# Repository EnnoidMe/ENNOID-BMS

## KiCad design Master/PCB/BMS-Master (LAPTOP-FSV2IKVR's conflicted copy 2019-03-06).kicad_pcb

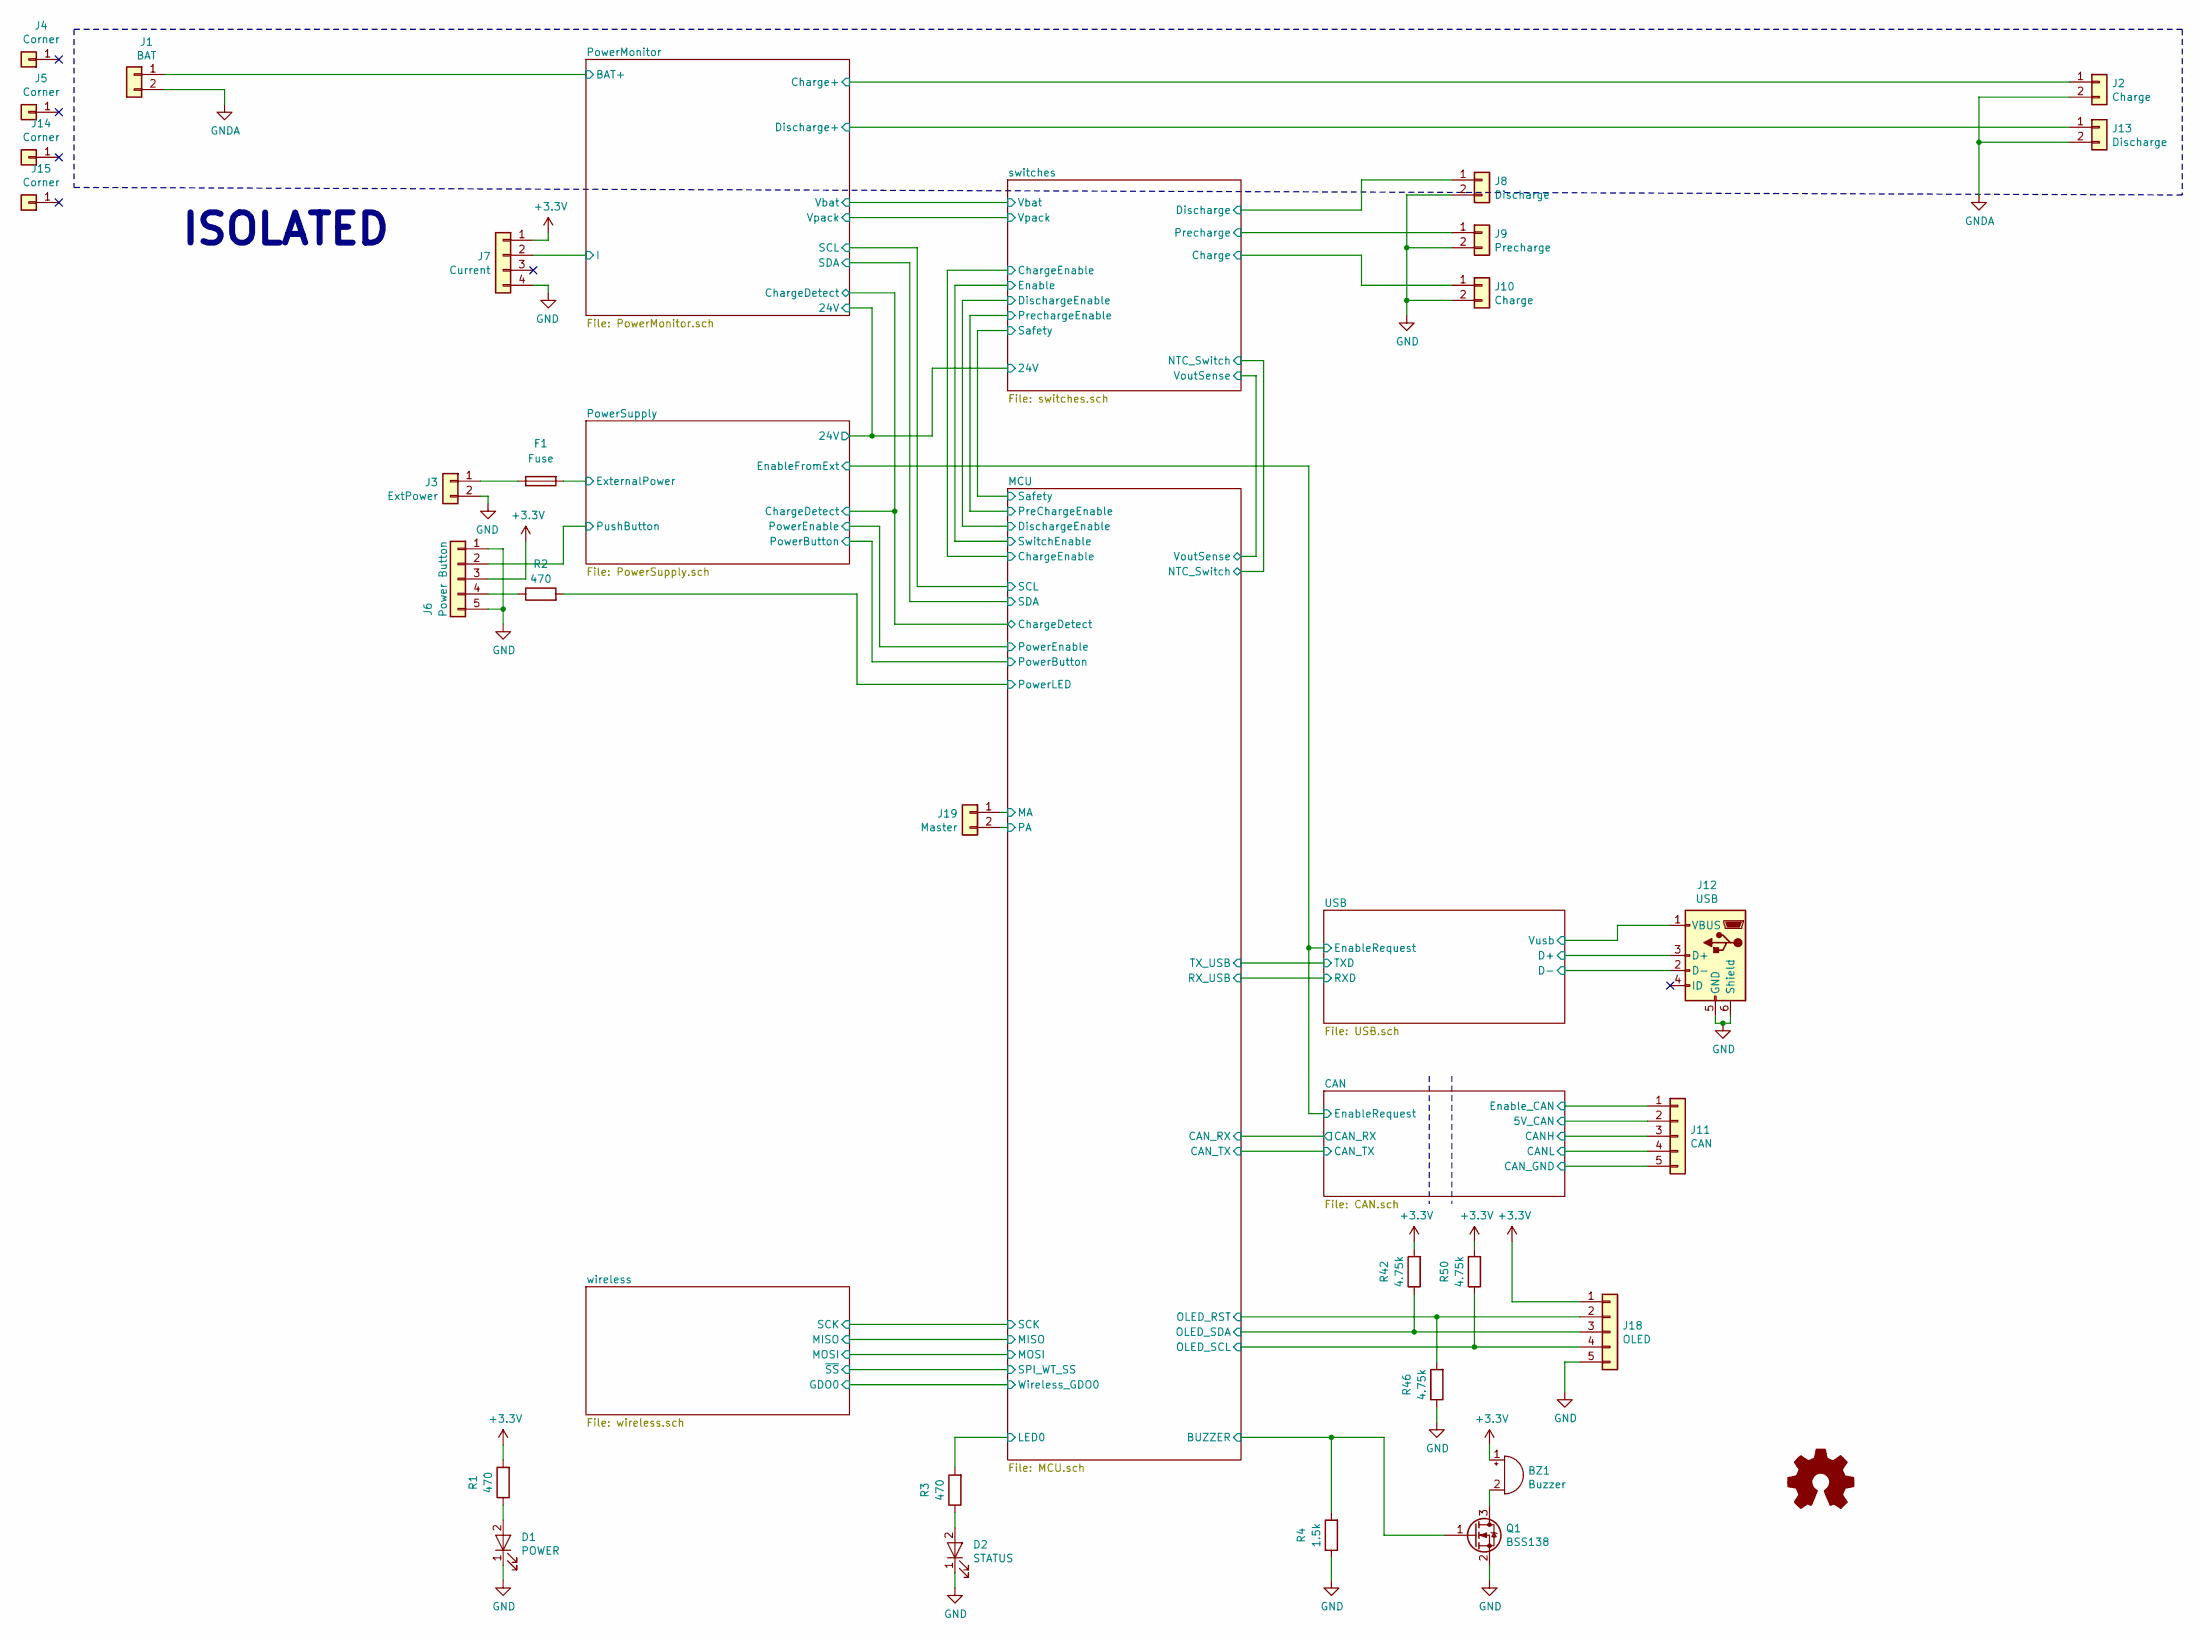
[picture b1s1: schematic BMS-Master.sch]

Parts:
BZ1: Buzzer; PUIAudio_SMT_0825_S_4_R
D1: POWER; LED_0603_HandSoldering
D2: STATUS; LED_0603_HandSoldering
F1: Fuse; Fuse_SMD1206_HandSoldering
J1: BAT; TerminalBlock_RND_205-00001_Pitch5.00mm
J2: Charge; TerminalBlock_RND_205-00001_Pitch5.00mm
J3: ExtPower; Molex_KK-6410-02_02x2.54mm_Straight
J4, J5, J14, J15: Corner; MountingHole_2.7mm_M2.5_Pad_Via
J6: Power Button; Molex_PicoBlade_53398-0571_05x1.25mm_Straight
J7: Current; Molex_KK-6410-04_04x2.54mm_Straight
J8: Discharge; Molex_KK-6410-02_02x2.54mm_Straight
J9: Precharge; Molex_KK-6410-02_02x2.54mm_Straight
J10: Charge; Molex_KK-6410-02_02x2.54mm_Straight
J11: CAN; Molex_PicoBlade_53261-0571_05x1.25mm_Angled
J12: USB; USB_Micro-B_Molex_47346-0001
J13: Discharge; TerminalBlock_RND_205-00001_Pitch5.00mm
J18: OLED; Molex_PicoBlade_53398-0571_05x1.25mm_Straight
J19: Master; Molex_KK-6410-02_02x2.54mm_Straight
LOGO1: Logo_Open_Hardware_Small; ENNOID-LOGO
Q1: BSS138; SOT-23
R1, R2, R3: 470; R_0603_HandSoldering
R4: 1.5k; R_0603_HandSoldering
R42, R46, R50: 4.75k; R_0603_HandSoldering

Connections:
/CAN/5V_CAN: J11.2; also elsewhere on the board
/CAN/CANH: J11.3; also elsewhere on the board
/CAN/CANL: J11.4; also elsewhere on the board
/CAN/CAN_GND: J11.5; also elsewhere on the board
/CAN/Enable_CAN: J11.1; also elsewhere on the board
/MCU/BUZZER: Q1.1 (G), R4.2; also elsewhere on the board
/MCU/LED0: R3.2; also elsewhere on the board
/MCU/MA: J19.1; also elsewhere on the board
/MCU/OLED_RST: J18.2, R46.2; also elsewhere on the board
/MCU/OLED_SCL: J18.4, R50.1; also elsewhere on the board
/MCU/OLED_SDA: J18.3, R42.1; also elsewhere on the board
/MCU/PA: J19.2; also elsewhere on the board
/MCU/PowerLED: R2.2; also elsewhere on the board
/PowerMonitor/24V: F1.2; also elsewhere on the board
/PowerMonitor/BAT+: J1.1; also elsewhere on the board
/PowerMonitor/Charge+: J2.1; also elsewhere on the board
/PowerMonitor/Discharge+: J13.1; also elsewhere on the board
/PowerMonitor/I: J7.2; also elsewhere on the board
/PowerSupply/PushButton: J6.2; also elsewhere on the board
/USB/D+: J12.3 (D+); also elsewhere on the board
/USB/D-: J12.2 (D-); also elsewhere on the board
/switches/Charge: J10.1; also elsewhere on the board
/switches/Discharge: J8.1; also elsewhere on the board
/switches/Precharge: J9.1; also elsewhere on the board
GND: D1.1 (K), D2.1 (K), J3.2, J6.1, J6.5, J7.4, J8.2, J9.2, J10.2, J12.5 (GND), J12.6 (Shield), J18.5, Q1.2 (S), R4.1, R46.1; also elsewhere on the board
GNDA: J1.2, J2.2, J13.2; also elsewhere on the board
unnamed: BZ1.2 (+), Q1.3 (D)
unnamed: D1.2 (A), R1.1
unnamed: D2.2 (A), R3.1
unnamed: F1.1, J3.1
unnamed: J6.4, R2.1
VDD: J12.1 (VBUS); also elsewhere on the board

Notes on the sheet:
ISOLATED

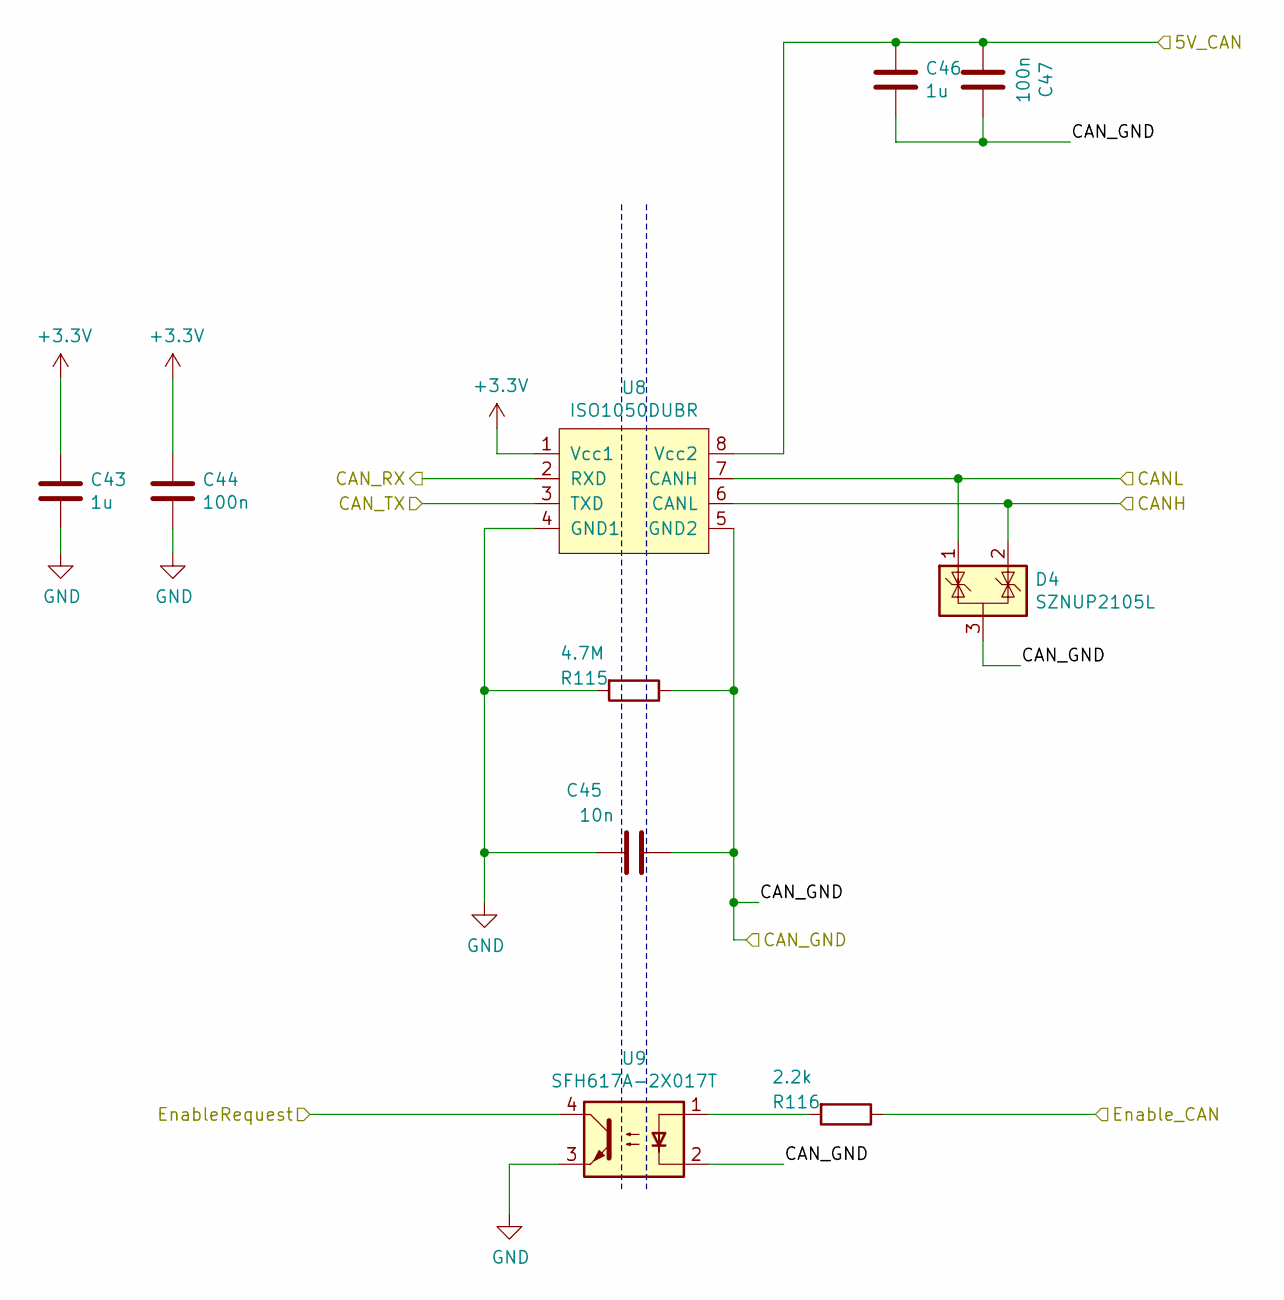
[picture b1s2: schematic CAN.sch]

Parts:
C43, C46: 1u; C_0805_HandSoldering
C44, C47: 100n; C_0603_HandSoldering
C45: 10n; C_0805_HandSoldering; Voltage 100V
D4: SZNUP2105L; SOT-23
R115: 4.7M; C_0805_HandSoldering; Voltage 100V
R116: 2.2k; C_0603_HandSoldering; Voltage 100V
U8: ISO1050DUBR; ISO1050
U9: SFH617A-2X017T; SMDIP-4_W9.53mm_Clearance8mm

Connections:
/CAN/5V_CAN: C46.1, C47.2, U8.8 (Vcc2); also elsewhere on the board
/CAN/CANH: D4.2 (K), U8.6 (CANL); also elsewhere on the board
/CAN/CANL: D4.1 (K), U8.7 (CANH); also elsewhere on the board
/CAN/CAN_GND: C45.1, C46.2, C47.1, D4.3 (A), R115.1, U8.5 (GND2), U9.2; also elsewhere on the board
/CAN/CAN_RX: U8.2 (RXD); also elsewhere on the board
/CAN/CAN_TX: U8.3 (TXD); also elsewhere on the board
/CAN/Enable_CAN: R116.1; also elsewhere on the board
/PowerSupply/EnableFromExt: U9.4; also elsewhere on the board
GND: C43.2, C44.2, C45.2, R115.2, U8.4 (GND1), U9.3; also elsewhere on the board
unnamed: R116.2, U9.1

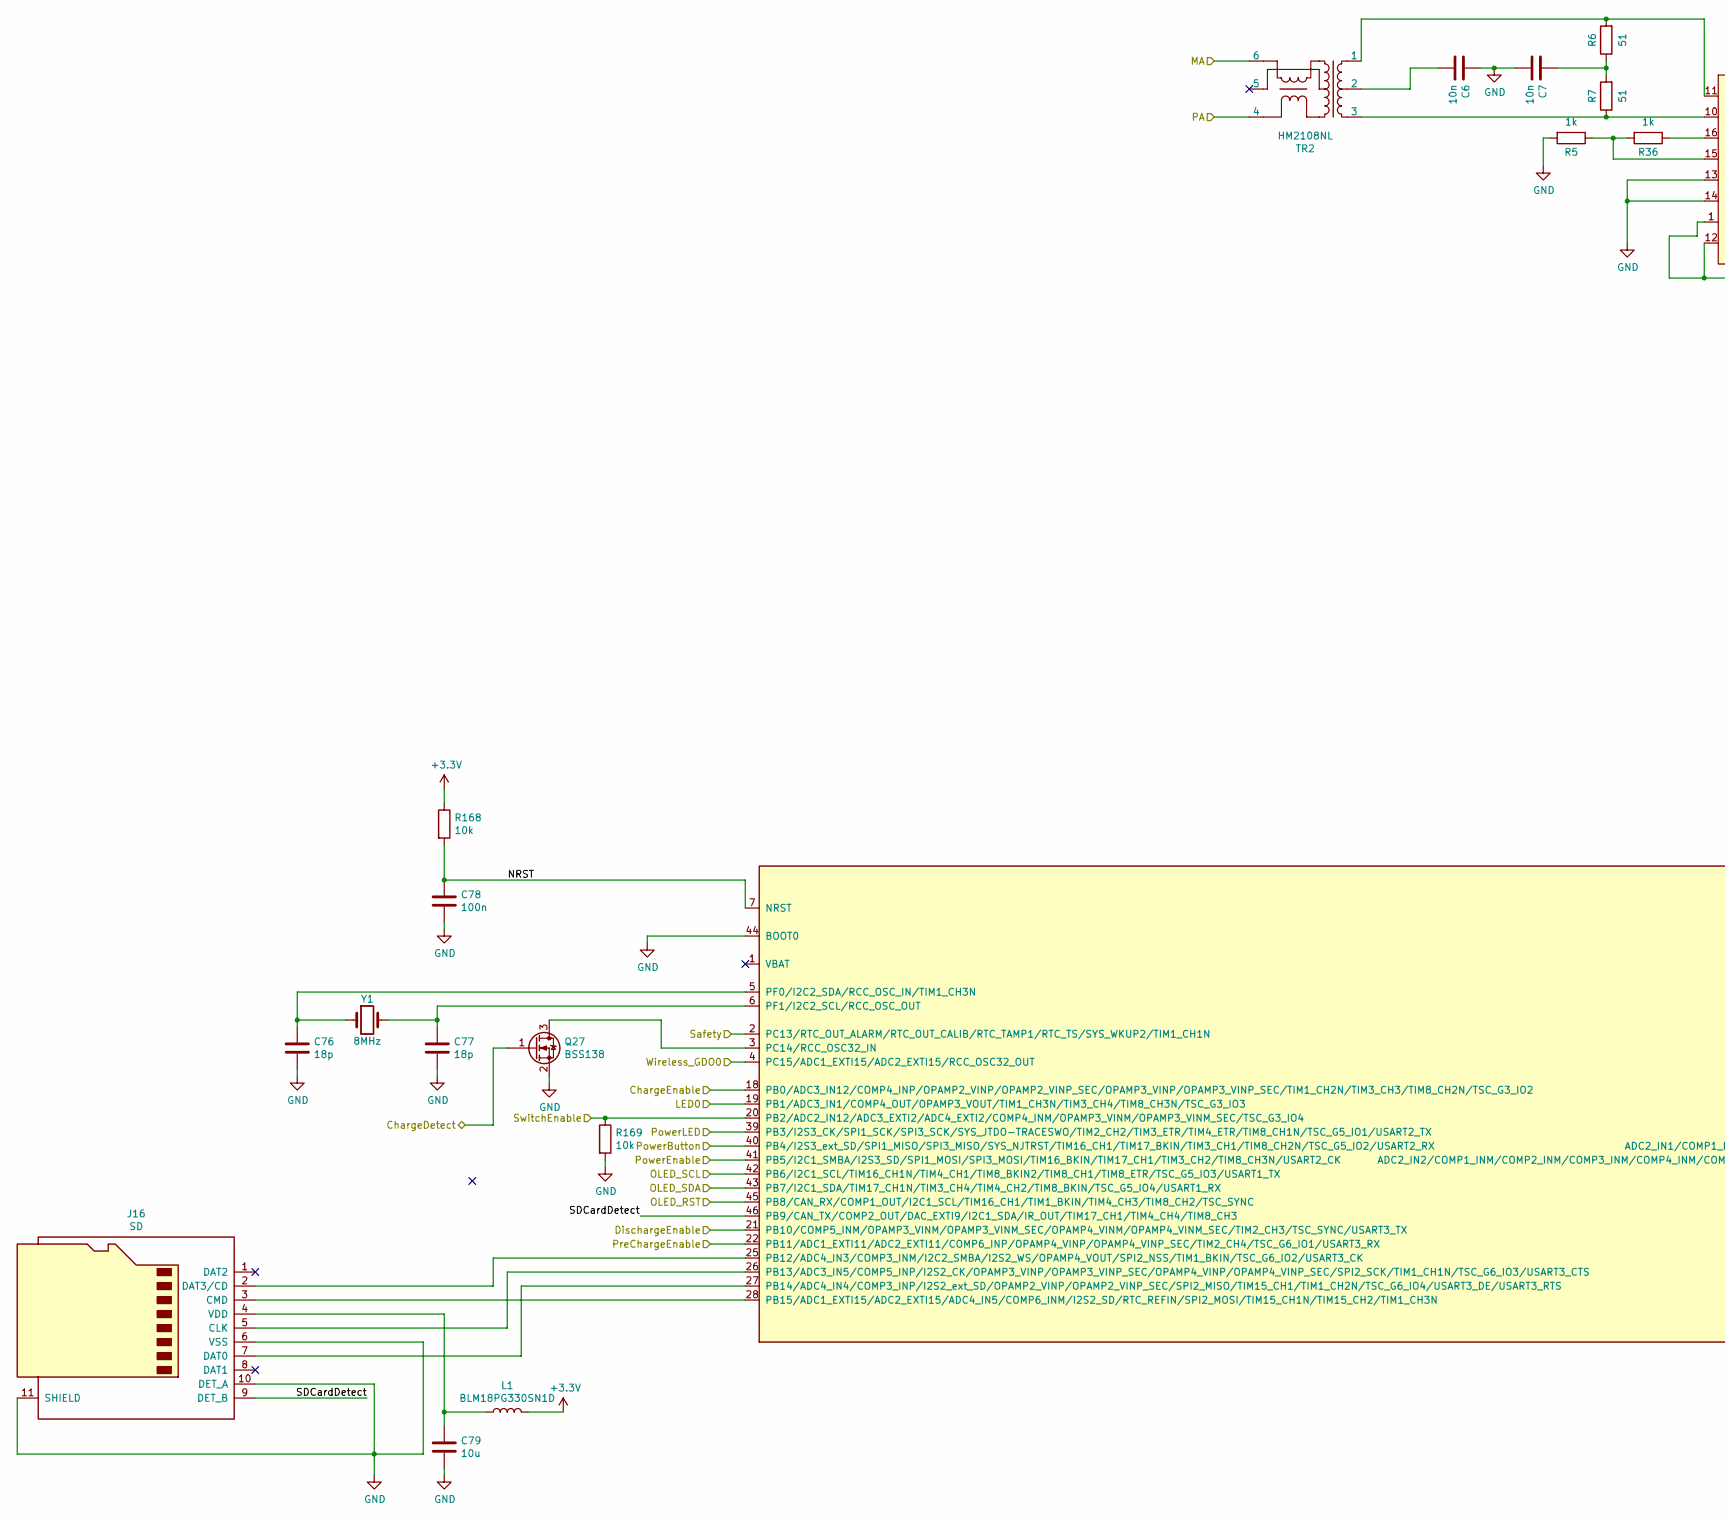
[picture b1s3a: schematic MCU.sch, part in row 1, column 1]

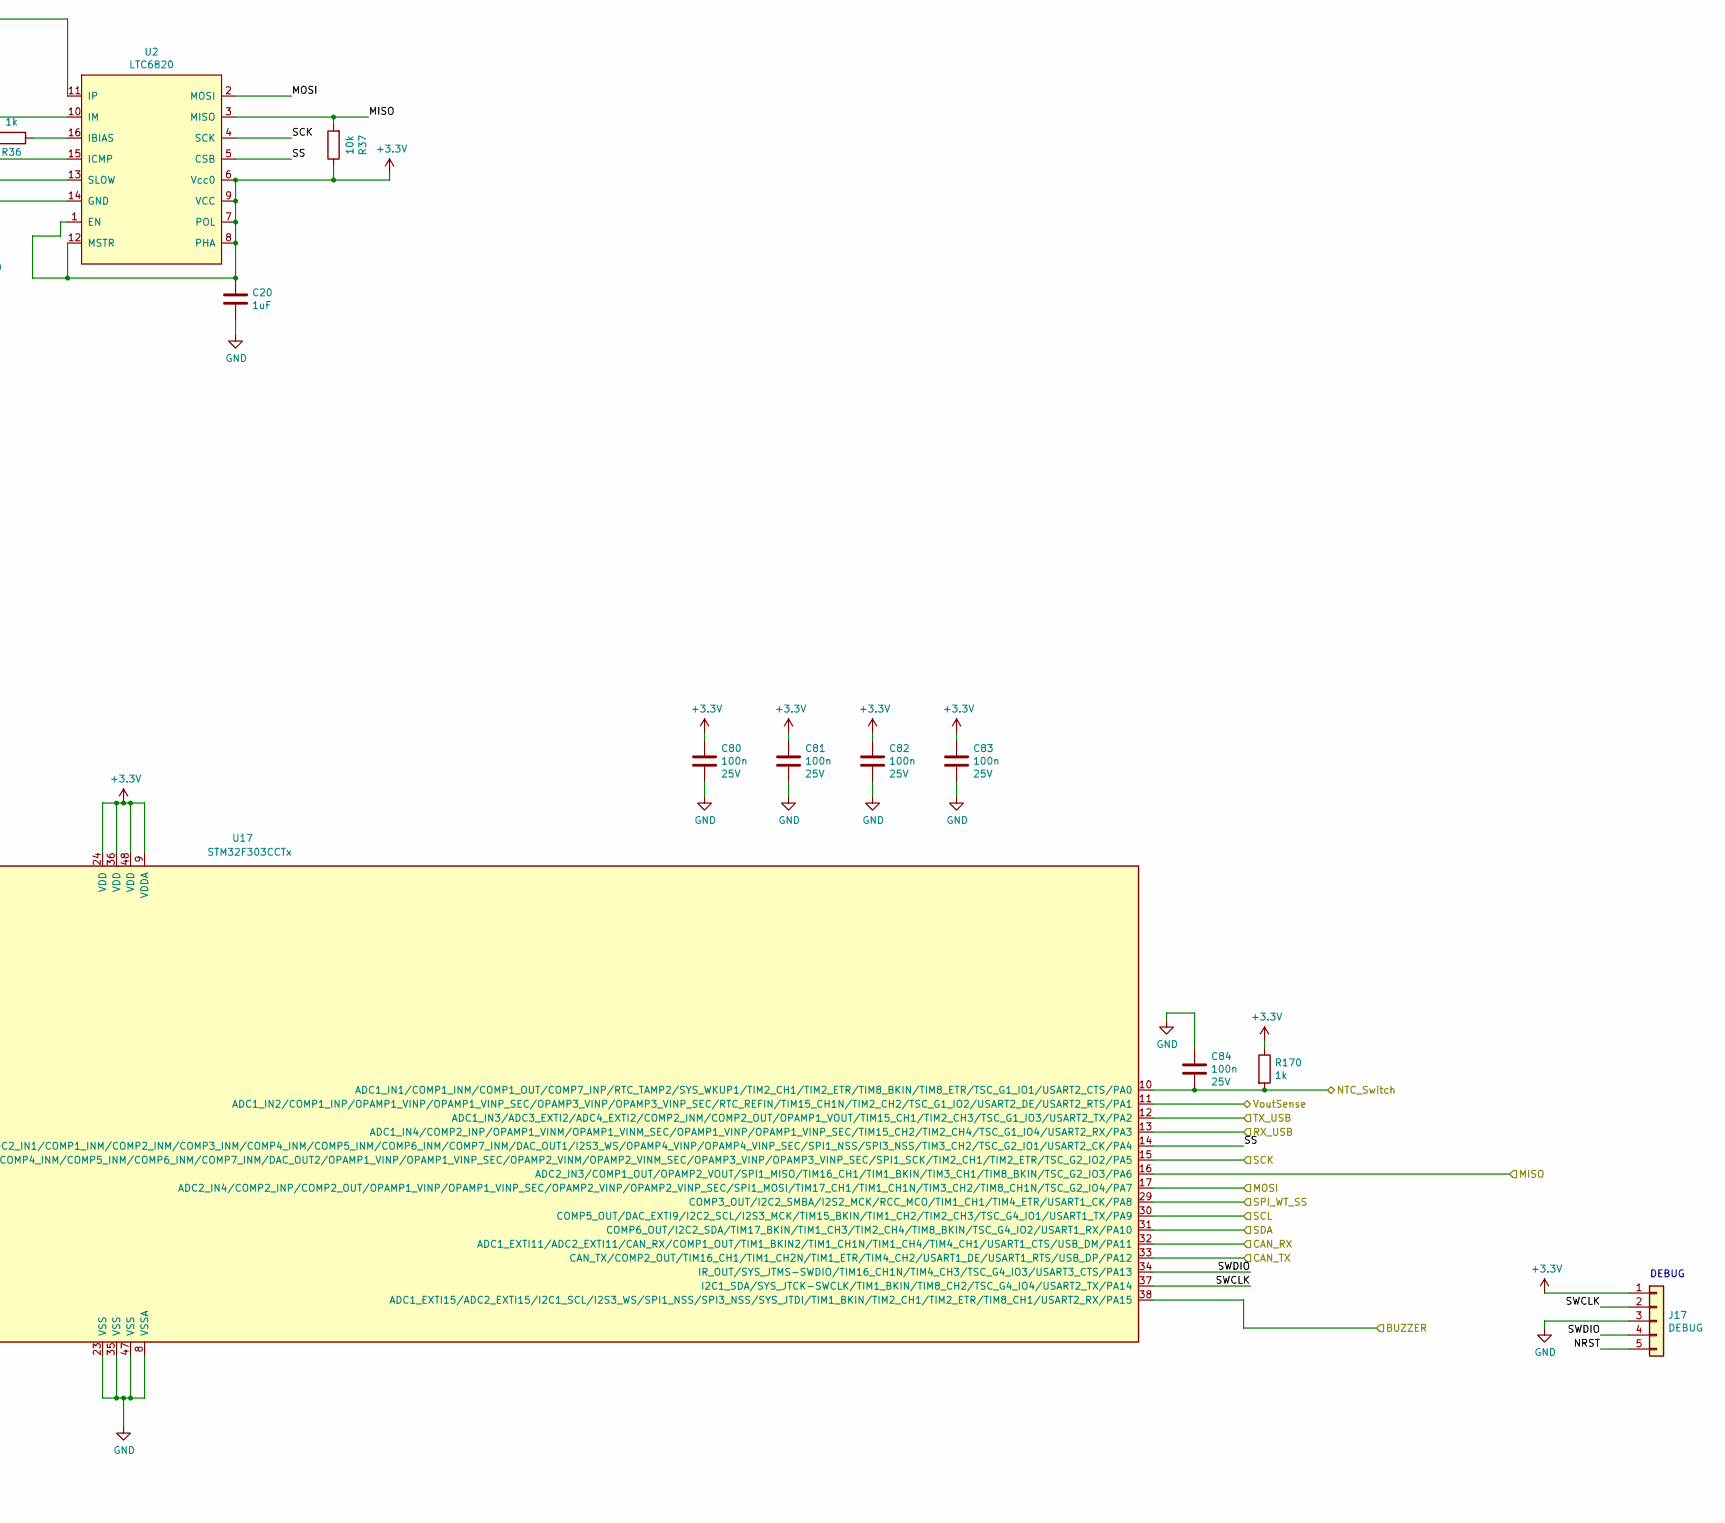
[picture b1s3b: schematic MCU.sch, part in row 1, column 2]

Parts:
C6, C7: 10n; C_0603_HandSoldering
C20: 1uF; C_0603_HandSoldering
C76, C77: 18p; C_0603_HandSoldering; Voltage 50V
C78: 100n; C_0603_HandSoldering
C79: 10u; C_0603_HandSoldering
C80, C81, C82, C83, C84: 100n; C_0603_HandSoldering; Voltage 25V
J16: SD; Hirose_DM3AT-SF-PEJM5
J17: DEBUG; Molex_PicoBlade_53261-0571_05x1.25mm_Angled
L1: BLM18PG330SN1D; L_0603_HandSoldering
Q27: BSS138; SOT-23
R5, R36, R170: 1k; R_0603_HandSoldering
R6, R7: 51; R_0603_HandSoldering
R37, R168, R169: 10k; R_0603_HandSoldering
TR2: HM2108NL
U2: LTC6820; MSOP-16_3x4mm_Pitch0.5mm
U17: STM32F303CCTx; LQFP-48_7x7mm_Pitch0.5mm
Y1: 8MHz; Crystal_SMD_Abracon_ABM3-2pin_5.0x3.2mm

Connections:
/CAN/CAN_RX: U17.32 (ADC1_EXTI11/ADC2_EXTI11/CAN_RX/COMP1_OU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); also elsewhere on the board
/CAN/CAN_TX: U17.33 (CAN_TX/COMP2_OUT/TIM16_CH1/TIM1_CH2N/TI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); also elsewhere on the board
/MCU/BUZZER: U17.38 (ADC1_EXTI15/ADC2_EXTI15/I2C1_SCL/I2S3_W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); also elsewhere on the board
/MCU/ChargeDetect: Q27.1 (G); also elsewhere on the board
/MCU/LED0: U17.19 (PB1/ADC3_IN1/COMP4_OUT/OPAMP3_VOUT/TIM1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); also elsewhere on the board
/MCU/MA: TR2.6; also elsewhere on the board
/MCU/MISO: R37.2, U2.3 (MISO), U17.16 (ADC2_IN3/COMP1_OUT/OPAMP2_VOUT/SPI1_MIS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); also elsewhere on the board
/MCU/MOSI: U2.2 (MOSI), U17.17 (ADC2_IN4/COMP2_INP/COMP2_OUT/OPAMP1_VIN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); also elsewhere on the board
/MCU/NRST: C78.1, J17.5, R168.2, U17.7 (NRST)
/MCU/NTC_Switch: C84.2, R170.2, U17.10 (ADC1_IN1/COMP1_INM/COMP1_OUT/COMP7_INP/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); also elsewhere on the board
/MCU/OLED_RST: U17.45 (PB8/CAN_RX/COMP1_OUT/I2C1_SCL/TIM16_CH1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); also elsewhere on the board
/MCU/OLED_SCL: U17.42 (PB6/I2C1_SCL/TIM16_CH1N/TIM4_CH1/TIM8_B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); also elsewhere on the board
/MCU/OLED_SDA: U17.43 (PB7/I2C1_SDA/TIM17_CH1N/TIM3_CH4/TIM4_C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); also elsewhere on the board
/MCU/PA: TR2.4; also elsewhere on the board
/MCU/PowerButton: U17.40 (PB4/I2S3_ext_SD/SPI1_MISO/SPI3_MISO/SYS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); also elsewhere on the board
/MCU/PowerEnable: U17.41 (PB5/I2C1_SMBA/I2S3_SD/SPI1_MOSI/SPI3_MO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); also elsewhere on the board
/MCU/PowerLED: U17.39 (PB3/I2S3_CK/SPI1_SCK/SPI3_SCK/SYS_JTDO-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); also elsewhere on the board
/MCU/PreChargeEnable: U17.22 (PB11/ADC1_EXTI11/ADC2_EXTI11/COMP6_INP/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); also elsewhere on the board
/MCU/SCK: U2.4 (SCK), U17.15 (ADC2_IN2/COMP1_INM/COMP2_INM/COMP3_INM/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); also elsewhere on the board
/MCU/SCL: U17.30 (COMP5_OUT/DAC_EXTI9/I2C2_SCL/I2S3_MCK/T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); also elsewhere on the board
/MCU/SDA: U17.31 (COMP6_OUT/I2C2_SDA/TIM17_BKIN/TIM1_CH3/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); also elsewhere on the board
/MCU/SDCardDetect: J16.9 (DET_B), U17.46 (PB9/CAN_TX/COMP2_OUT/DAC_EXTI9/I2C1_SDA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)
/MCU/SPI_WT_SS: U17.29 (COMP3_OUT/I2C2_SMBA/I2S2_MCK/RCC_MCO/TI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); also elsewhere on the board
/MCU/SS: U2.5 (CSB), U17.14 (ADC2_IN1/COMP1_INM/COMP2_INM/COMP3_INM/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)
/MCU/SWCLK: J17.2, U17.37 (I2C1_SDA/SYS_JTCK-SWCLK/TIM1_BKIN/TIM8_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)
/MCU/SWDIO: J17.4, U17.34 (IR_OUT/SYS_JTMS-SWDIO/TIM16_CH1N/TIM4_C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)
/MCU/Safety: U17.2 (PC13/RTC_OUT_ALARM/RTC_OUT_CALIB/RTC_TA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); also elsewhere on the board
/MCU/VoutSense: U17.11 (ADC1_IN2/COMP1_INP/OPAMP1_VINP/OPAMP1_V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); also elsewhere on the board
/USB/RXD: U17.13 (ADC1_IN4/COMP2_INP/OPAMP1_VINM/OPAMP1_V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); also elsewhere on the board
/USB/TXD: U17.12 (ADC1_IN3/ADC3_EXTI2/ADC4_EXTI2/COMP2_IN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); also elsewhere on the board
/switches/Enable: R169.1, U17.20 (PB2/ADC2_IN12/ADC3_EXTI2/ADC4_EXTI2/COM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); also elsewhere on the board
/wireless/GDO0: U17.4 (PC15/ADC1_EXTI15/ADC2_EXTI15/RCC_OSC32_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); also elsewhere on the board
GND: C6.2, C7.1, C20.1, C76.2, C77.2, C78.2, C79.2, C80.2, C81.2, C82.2, C83.2, C84.1, J16.6 (VSS), J16.10 (DET_A), J16.11 (SHIELD), J17.3, Q27.2 (S), R5.2, R169.2, U2.13 (SLOW), U2.14 (GND), U17.8 (VSSA), U17.23 (VSS), U17.35 (VSS), U17.44 (BOOT0), U17.47 (VSS); also elsewhere on the board
unnamed: C6.1, TR2.2
unnamed: C7.2, R6.1, R7.2
unnamed: C76.1, U17.5 (PF0/I2C2_SDA/RCC_OSC_IN/TIM1_CH3N), Y1.1
unnamed: C77.1, U17.6 (PF1/I2C2_SCL/RCC_OSC_OUT), Y1.2
unnamed: C79.1, J16.4 (VDD), L1.1
unnamed: J16.2 (DAT3/CD), U17.25 (PB12/ADC4_IN3/COMP3_INM/I2C2_SMBA/I2S2_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)
unnamed: J16.3 (CMD), U17.28 (PB15/ADC1_EXTI15/ADC2_EXTI15/ADC4_IN5/C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)
unnamed: J16.5 (CLK), U17.26 (PB13/ADC3_IN5/COMP5_INP/I2S2_CK/OPAMP3_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)
unnamed: J16.7 (DAT0), U17.27 (PB14/ADC4_IN4/COMP3_INP/I2S2_ext_SD/OPA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)
unnamed: Q27.3 (D), U17.3 (PC14/RCC_OSC32_IN)
unnamed: R6.2, TR2.1, U2.11 (IP)
unnamed: R7.1, TR2.3, U2.10 (IM)
unnamed: R36.1, U2.16 (IBIAS)
unnamed: R5.1, R36.2, U2.15 (ICMP)

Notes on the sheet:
DEBUG

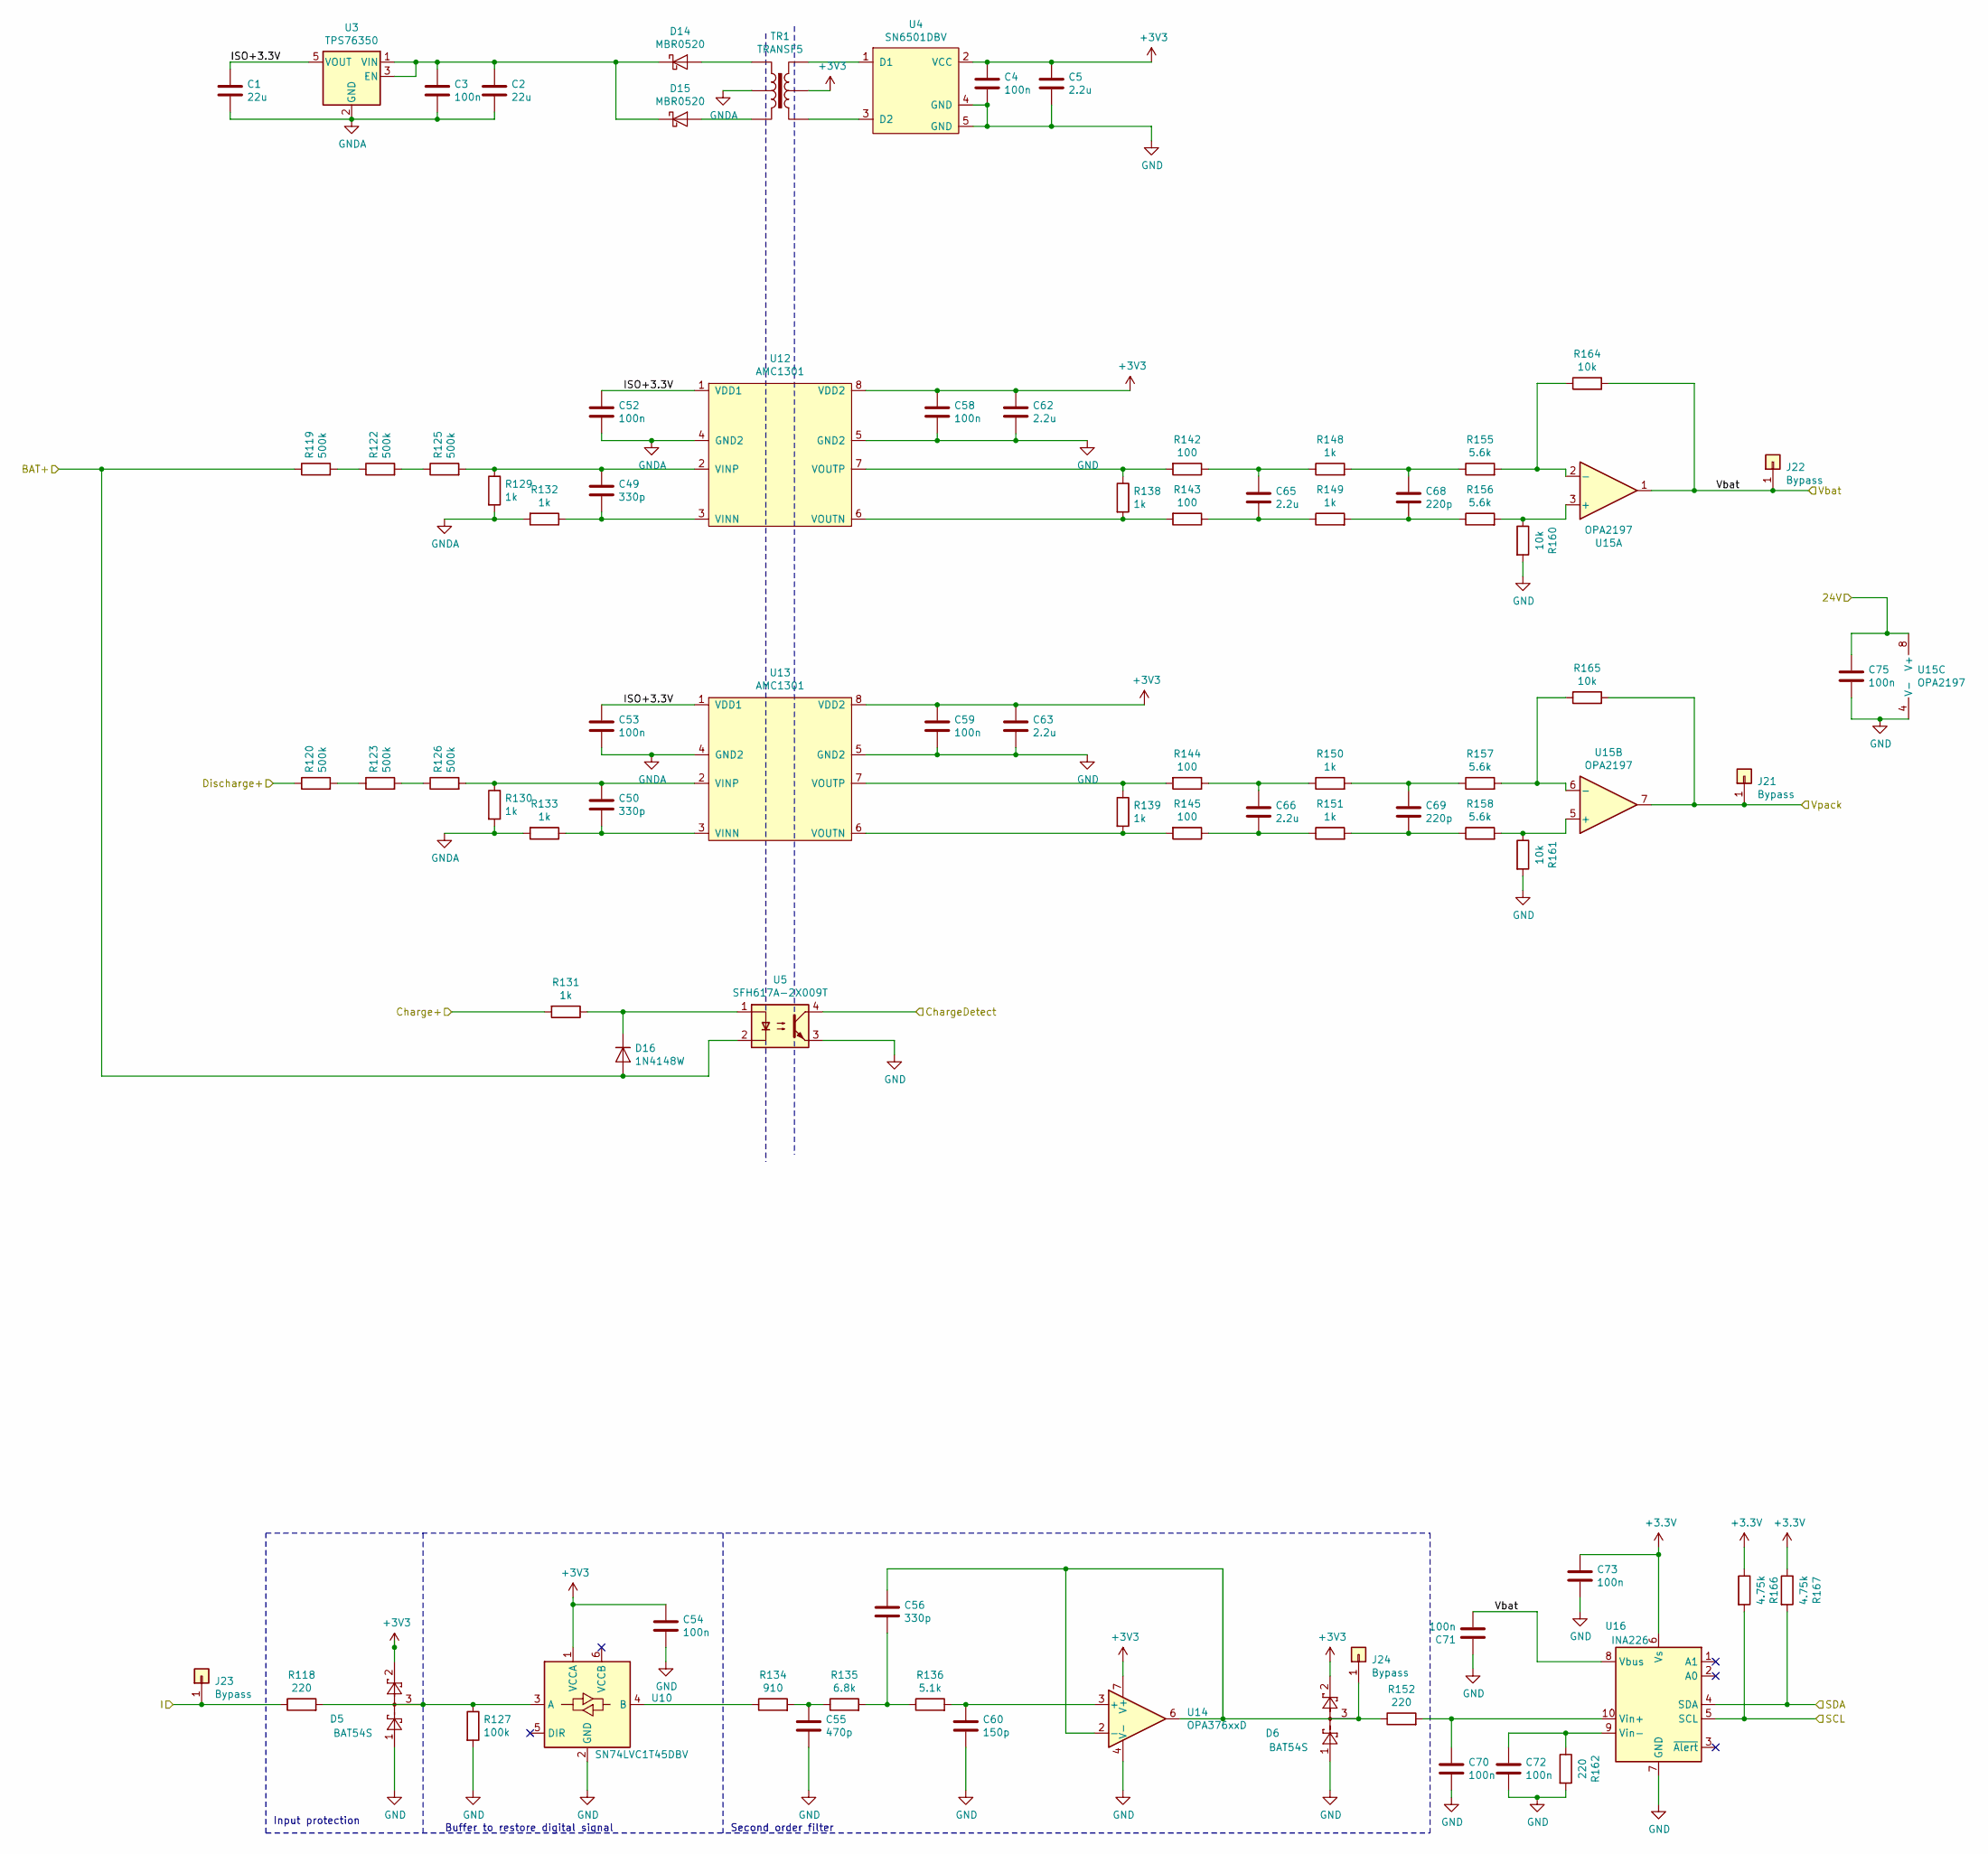
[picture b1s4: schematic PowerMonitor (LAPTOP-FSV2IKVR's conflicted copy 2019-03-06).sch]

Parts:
C1, C2: 22u; C_0805_HandSoldering
C3, C4, C52, C53, C54, C58, C59, C70, C71, C72, C73, C75: 100n; C_0603_HandSoldering
C5, C62, C63, C65, C66: 2.2u; C_0603_HandSoldering
C49, C50, C56: 330p; C_0603_HandSoldering
C55: 470p; C_0603_HandSoldering
C60: 150p; C_0603_HandSoldering
C68, C69: 220p; C_0603_HandSoldering
D5, D6: BAT54S; SOT-23
D14, D15: MBR0520; D_SOD-123
D16: 1N4148W; D_SOD-123
J21, J22, J23, J24: Bypass; TestPoint_Loop_D2.54mm_Drill1.5mm_Beaded
R118, R152, R162: 220; R_0603_HandSoldering
R119, R120, R122, R123, R125, R126: 500k; R_1206
R127: 100k; R_0603_HandSoldering
R129, R130, R131, R132, R133, R138, R139, R148, R149, R150, R151: 1k; R_0603_HandSoldering
R134: 910; R_0603_HandSoldering
R135: 6.8k; R_0603_HandSoldering
R136: 5.1k; R_0603_HandSoldering
R142, R143, R144, R145: 100; R_0603_HandSoldering
R155, R156, R157, R158: 5.6k; R_0603_HandSoldering
R160, R161, R164, R165: 10k; R_0603_HandSoldering
R166, R167: 4.75k; R_0603_HandSoldering
TR1: TRANSF5; WURTH-760390014
U3: TPS76350; SOT-23-5_HandSoldering
U4: SN6501DBV; SOT-23-5_HandSoldering
U5: SFH617A-2X009T; SMDIP-4_W7.62mm
U10: SN74LVC1T45DBV; SOT-23-6
U12, U13: AMC1301; SSO-8_6.8x5.9mm_Pitch1.27mm_Clearance8mm
U14: OPA376xxD; SOIC-8_3.9x4.9mm_Pitch1.27mm
U15: OPA2197; SOIC-8_3.9x4.9mm_Pitch1.27mm
U16: INA226; MSOP-10_3x3mm_Pitch0.5mm

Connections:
/MCU/ChargeDetect: U5.4; also elsewhere on the board
/MCU/SCL: R166.2, U16.5 (SCL); also elsewhere on the board
/MCU/SDA: R167.2, U16.4 (SDA); also elsewhere on the board
/PowerMonitor/24V: C75.1, U15.8 (V+); also elsewhere on the board
/PowerMonitor/BAT+: D16.2 (A), R119.1, U5.2; also elsewhere on the board
/PowerMonitor/Charge+: R131.2; also elsewhere on the board
/PowerMonitor/Discharge+: R120.1; also elsewhere on the board
/PowerMonitor/I: J23.1, R118.1; also elsewhere on the board
/PowerMonitor/ISO+3.3V: C1.1, C52.1, C53.1, U3.5 (VOUT), U12.1 (VDD1), U13.1 (VDD1)
/PowerMonitor/Vbat: C71.1, J22.1, R164.2, U15.1, U16.8 (Vbus); also elsewhere on the board
/PowerMonitor/Vpack: J21.1, R165.2, U15.7; also elsewhere on the board
GND: C4.2, C5.2, C54.1, C55.1, C58.2, C59.2, C60.1, C62.2, C63.2, C70.1, C71.2, C72.1, C73.1, C75.2, D5.1, D6.1, R127.2, R160.2, R161.2, R162.2, U4.4 (GND), U4.5 (GND), U5.3, U10.2 (GND), U12.5 (GND2), U13.5 (GND2), U14.4 (V-), U15.4 (V-), U16.7 (GND); also elsewhere on the board
GNDA: C1.2, C2.2, C3.2, C52.2, C53.2, R129.2, R130.2, R132.2, R133.2, TR1.2, U3.2 (GND), U12.4 (GND2), U13.4 (GND2); also elsewhere on the board
unnamed: C2.1, C3.1, D14.1 (K), D15.1 (K), U3.1 (VIN), U3.3 (EN)
unnamed: C49.1, R125.2, R129.1, U12.2 (VINP)
unnamed: C49.2, R132.1, U12.3 (VINN)
unnamed: C50.1, R126.2, R130.1, U13.2 (VINP)
unnamed: C50.2, R133.1, U13.3 (VINN)
unnamed: C55.2, R134.2, R135.1
unnamed: C56.1, R135.2, R136.1
unnamed: C56.2, D6.3, J24.1, R152.1, U14.2 (-), U14.6
unnamed: C60.2, R136.2, U14.3 (+)
unnamed: C65.1, R142.1, R148.1
unnamed: C65.2, R143.1, R149.1
unnamed: C66.1, R144.1, R150.1
unnamed: C66.2, R145.1, R151.1
unnamed: C68.1, R148.2, R155.1
unnamed: C68.2, R149.2, R156.1
unnamed: C69.1, R150.2, R157.1
unnamed: C69.2, R151.2, R158.1
unnamed: C70.2, R152.2, U16.10 (Vin+)
unnamed: C72.2, R162.1, U16.9 (Vin-)
unnamed: D5.3, R118.2, R127.1, U10.3 (A)
unnamed: D14.2 (A), TR1.1
unnamed: D15.2 (A), TR1.3
unnamed: D16.1 (K), R131.1, U5.1
unnamed: R119.2, R122.1
unnamed: R120.2, R123.1
unnamed: R122.2, R125.1
unnamed: R123.2, R126.1
unnamed: R134.1, U10.4 (B)
unnamed: R138.1, R142.2, U12.7 (VOUTP)
unnamed: R138.2, R143.2, U12.6 (VOUTN)
unnamed: R139.1, R144.2, U13.7 (VOUTP)
unnamed: R139.2, R145.2, U13.6 (VOUTN)
unnamed: R155.2, R164.1, U15.2 (-)
unnamed: R156.2, R160.1, U15.3 (+)
unnamed: R157.2, R165.1, U15.6 (-)
unnamed: R158.2, R161.1, U15.5 (+)
unnamed: TR1.4, U4.3 (D2)
unnamed: TR1.6, U4.1 (D1)

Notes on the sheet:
Input protection
Buffer to restore digital signal
Second order filter
